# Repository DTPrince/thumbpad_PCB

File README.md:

# thumbpad_PCB
Repo for thumbstick PCB design

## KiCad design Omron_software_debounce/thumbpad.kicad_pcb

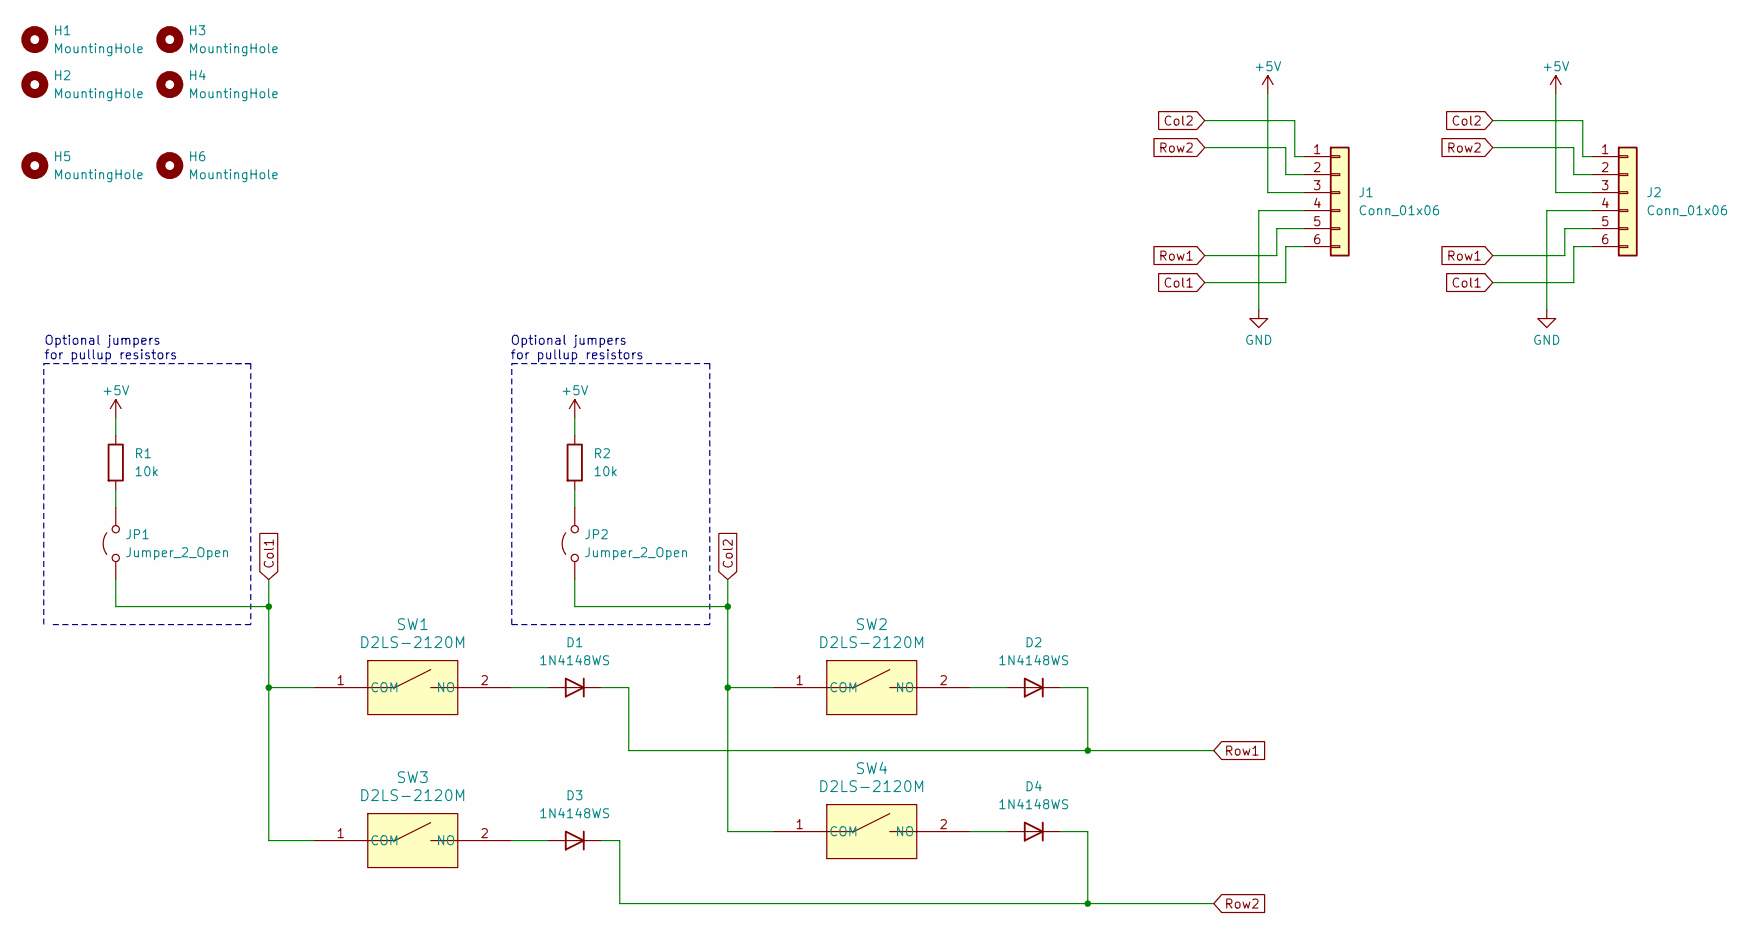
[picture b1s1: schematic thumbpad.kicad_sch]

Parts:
D1, D2, D3, D4: 1N4148WS; D_SOD-323
H1, H2, H3, H4: MountingHole; MountingHole_3.2mm_M3_ISO7380
H5, H6: MountingHole; MountingHole_1.6mm
J1: Conn_01x06; TEAmp-CON6-84953-SMT-RA-FCC-FPC
J2: Conn_01x06; pads_connector_0.1mm
JP1, JP2: Jumper_2_Open; SolderJumper-2_P1.3mm_Open_Pad1.0x1.5mm
R1, R2: 10k; R_0805_2012Metric_Pad1.20x1.40mm_HandSolder
SW1, SW2, SW3, SW4: D2LS-2120M; Omron_SW_D2LS_11_20M

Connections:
+5V: J1.3, J2.3, R1.1, R2.1
Col1: J1.6, J2.6, JP1.1 (A), SW1.1 (COM), SW3.1 (COM)
Col2: J1.1, J2.1, JP2.1 (A), SW2.1 (COM), SW4.1 (COM)
GND: J1.4, J2.4
unnamed: D1.2 (A), SW1.2 (NO)
unnamed: D2.2 (A), SW2.2 (NO)
unnamed: D3.2 (A), SW3.2 (NO)
unnamed: D4.2 (A), SW4.2 (NO)
unnamed: JP1.2 (B), R1.2
unnamed: JP2.2 (B), R2.2
Row1: D1.1 (K), D2.1 (K), J1.5, J2.5
Row2: D3.1 (K), D4.1 (K), J1.2, J2.2

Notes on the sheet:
Optional jumpers for pullup resistors

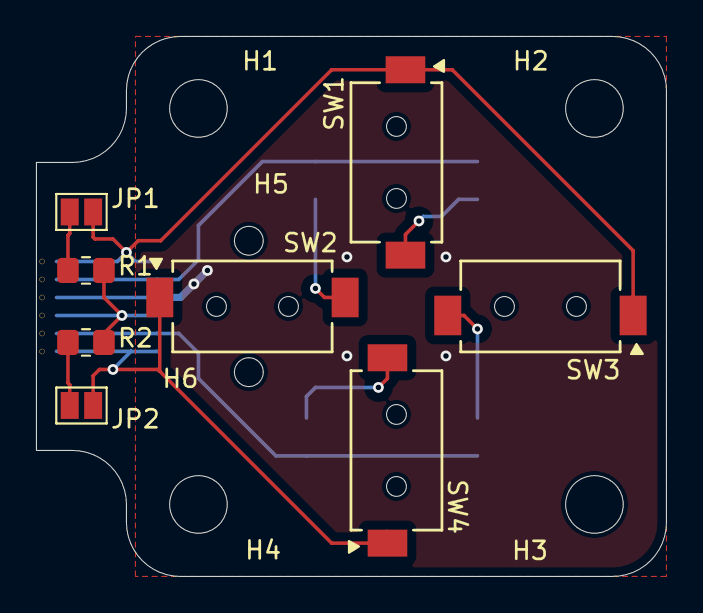
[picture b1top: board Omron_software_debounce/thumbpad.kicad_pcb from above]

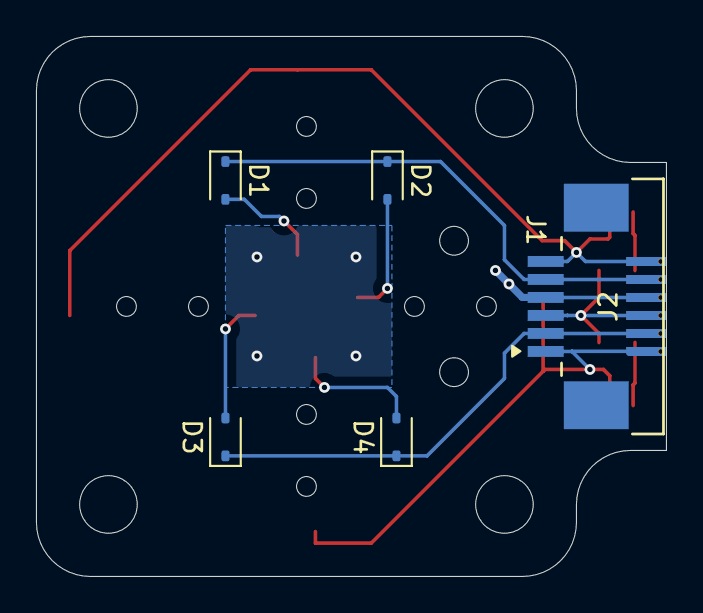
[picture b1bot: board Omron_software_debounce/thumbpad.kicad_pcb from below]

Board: 2 copper layers, 35.0 x 30.0 mm, 20 parts (6 on the bottom side), 12 nets.

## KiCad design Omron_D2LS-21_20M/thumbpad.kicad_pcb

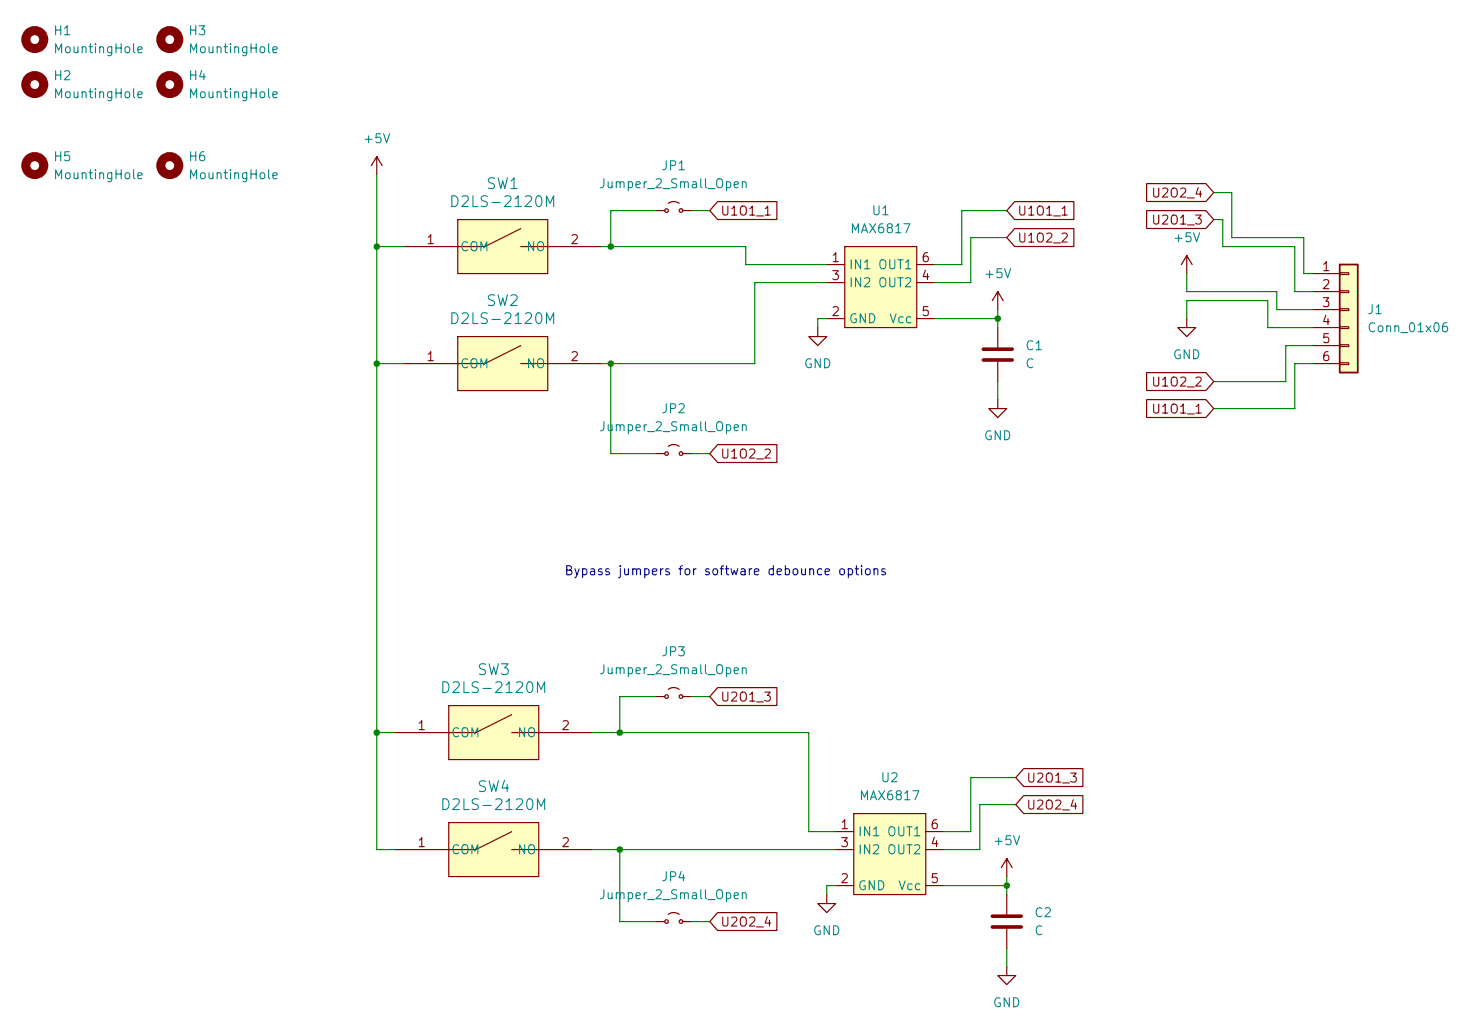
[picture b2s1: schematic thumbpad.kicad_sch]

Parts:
C1, C2: C; C_0805_2012Metric_Pad1.18x1.45mm_HandSolder
H1, H2, H3, H4: MountingHole; MountingHole_3.2mm_M3_ISO7380
H5, H6: MountingHole; MountingHole_1.6mm
J1: Conn_01x06; TEAmp-CON6-84953-SMT-RA-FCC-FPC
JP1, JP2, JP3, JP4: Jumper_2_Small_Open; SolderJumper-2_P1.3mm_Open_Pad1.0x1.5mm
SW1, SW2, SW3, SW4: D2LS-2120M; Omron_SW_D2LS_11_20M
U1, U2: MAX6817; SOT-23-6

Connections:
+5V: C1.1, C2.1, J1.3, SW1.1 (COM), SW2.1 (COM), SW3.1 (COM), SW4.1 (COM), U1.5 (Vcc), U2.5 (Vcc)
GND: C1.2, C2.2, J1.4, U1.2 (GND), U2.2 (GND)
unnamed: JP1.1 (A), SW1.2 (NO), U1.1 (IN1)
unnamed: JP2.1 (A), SW2.2 (NO), U1.3 (IN2)
unnamed: JP3.1 (A), SW3.2 (NO), U2.1 (IN1)
unnamed: JP4.1 (A), SW4.2 (NO), U2.3 (IN2)
U1O1_1: J1.6, JP1.2 (B), U1.6 (OUT1)
U1O2_2: J1.5, JP2.2 (B), U1.4 (OUT2)
U2O1_3: J1.2, JP3.2 (B), U2.6 (OUT1)
U2O2_4: J1.1, JP4.2 (B), U2.4 (OUT2)

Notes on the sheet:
Bypass jumpers for software debounce options

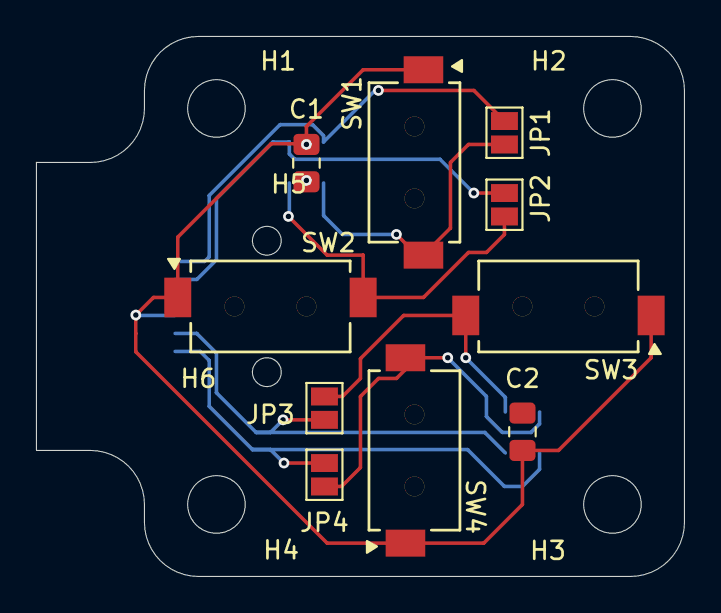
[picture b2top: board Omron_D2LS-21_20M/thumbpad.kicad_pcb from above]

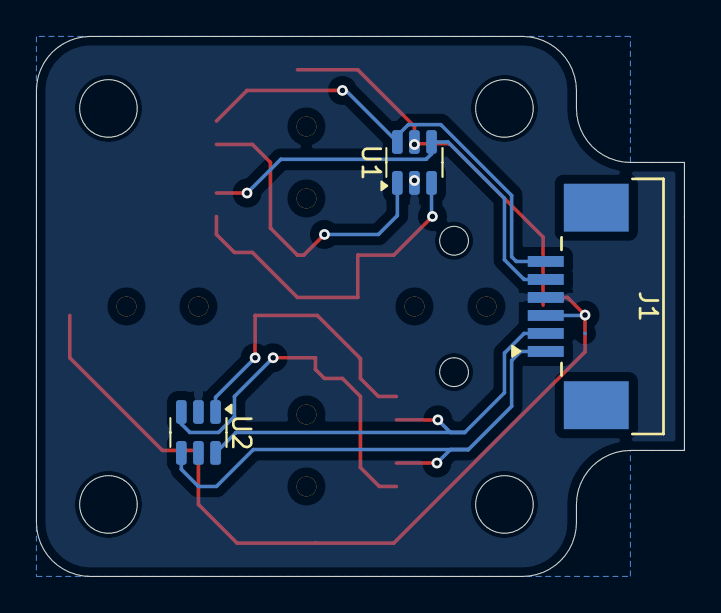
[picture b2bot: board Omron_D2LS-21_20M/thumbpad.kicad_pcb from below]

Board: 2 copper layers, 36.0 x 30.0 mm, 19 parts (3 on the bottom side), 10 nets.

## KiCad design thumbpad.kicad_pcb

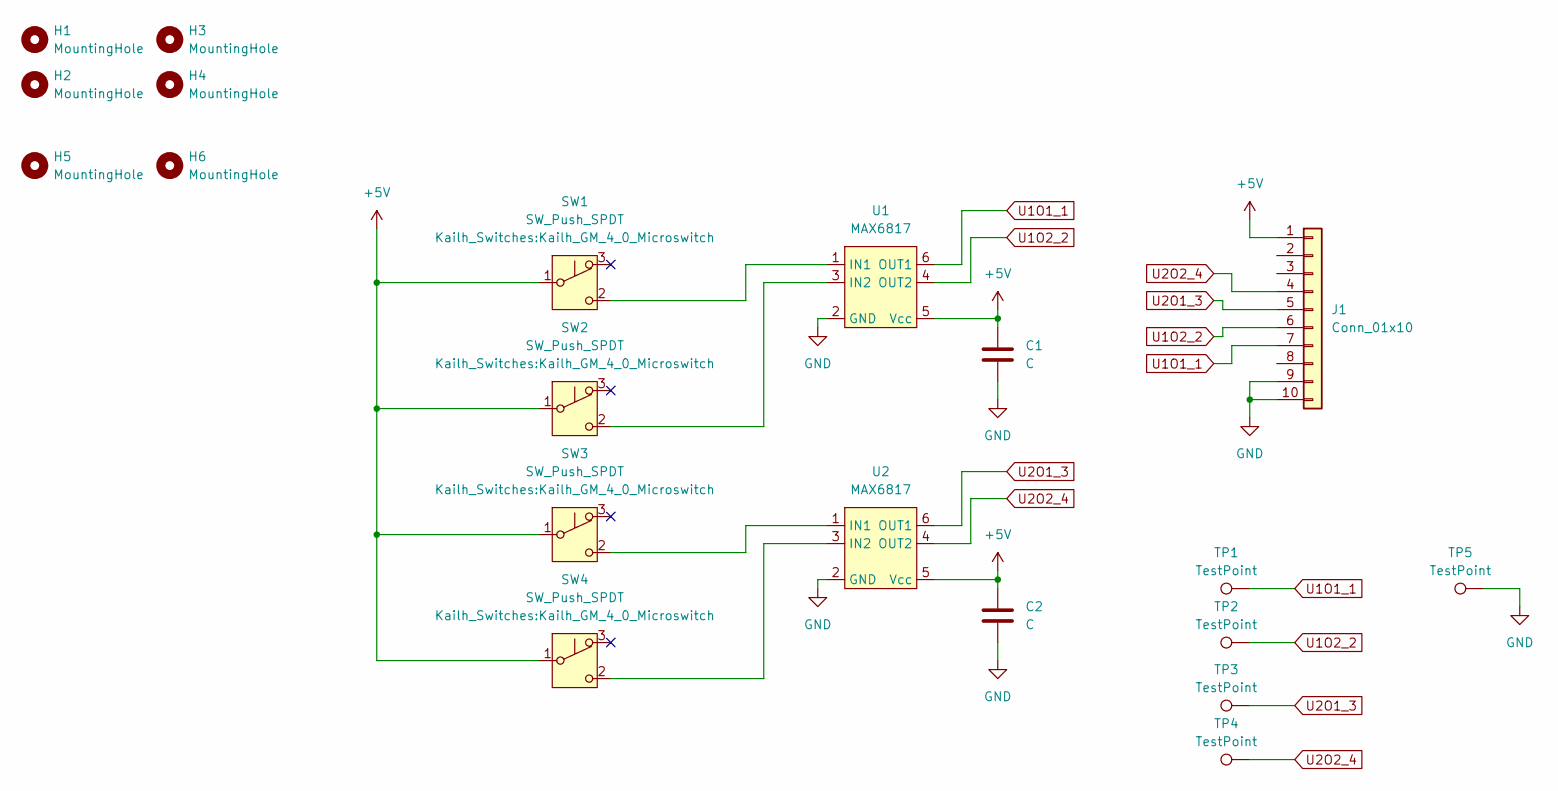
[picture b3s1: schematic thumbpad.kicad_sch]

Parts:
C1, C2: C; C_0805_2012Metric_Pad1.18x1.45mm_HandSolder
H1, H2, H3, H4: MountingHole; MountingHole_3.2mm_M3_ISO7380
H5, H6: MountingHole; MountingHole_1.6mm
J1: Conn_01x10; TE_1-84952-0_1x10-1MP_P1.0mm_Horizontal
SW1, SW2, SW3, SW4: SW_Push_SPDT; Kailh_GM_4_0_Microswitch
TP1, TP2, TP3, TP4: TestPoint; TestPoint_Pad_2.0x2.0mm
TP5: TestPoint; TestPoint_Loop_D2.60mm_Drill1.6mm_Beaded
U1, U2: MAX6817; SOT-23-6

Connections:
+5V: C1.1, C2.1, J1.1, SW1.1 (A), SW2.1 (A), SW3.1 (A), SW4.1 (A), U1.5 (Vcc), U2.5 (Vcc)
GND: C1.2, C2.2, J1.9, J1.10, TP5.1, U1.2 (GND), U2.2 (GND)
unnamed: SW1.2 (B), U1.1 (IN1)
unnamed: SW2.2 (B), U1.3 (IN2)
unnamed: SW3.2 (B), U2.1 (IN1)
unnamed: SW4.2 (B), U2.3 (IN2)
U1O1_1: J1.7, TP1.1, U1.6 (OUT1)
U1O2_2: J1.6, TP2.1, U1.4 (OUT2)
U2O1_3: J1.5, TP3.1, U2.6 (OUT1)
U2O2_4: J1.4, TP4.1, U2.4 (OUT2)

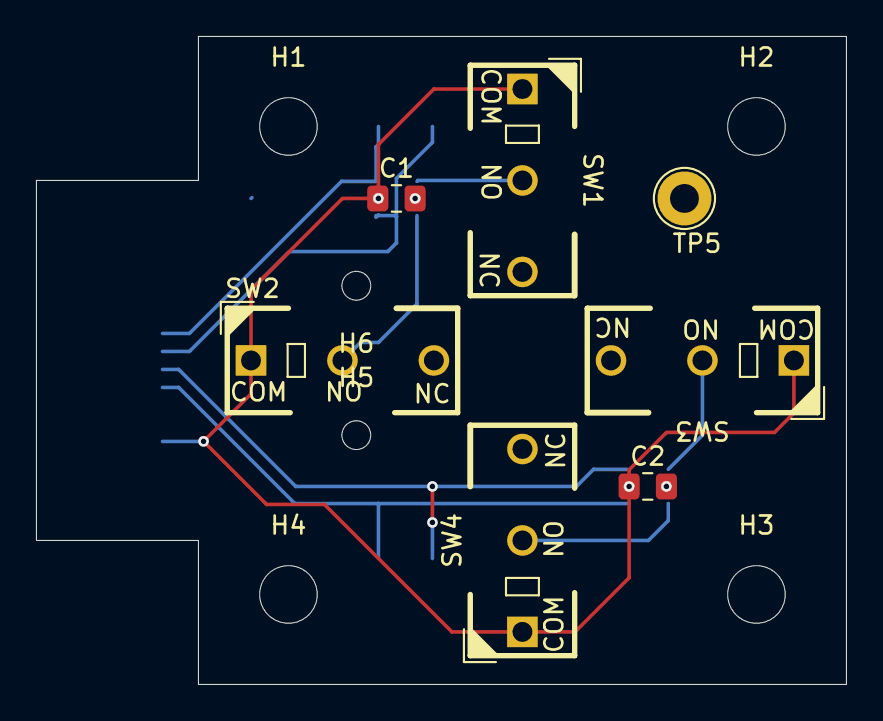
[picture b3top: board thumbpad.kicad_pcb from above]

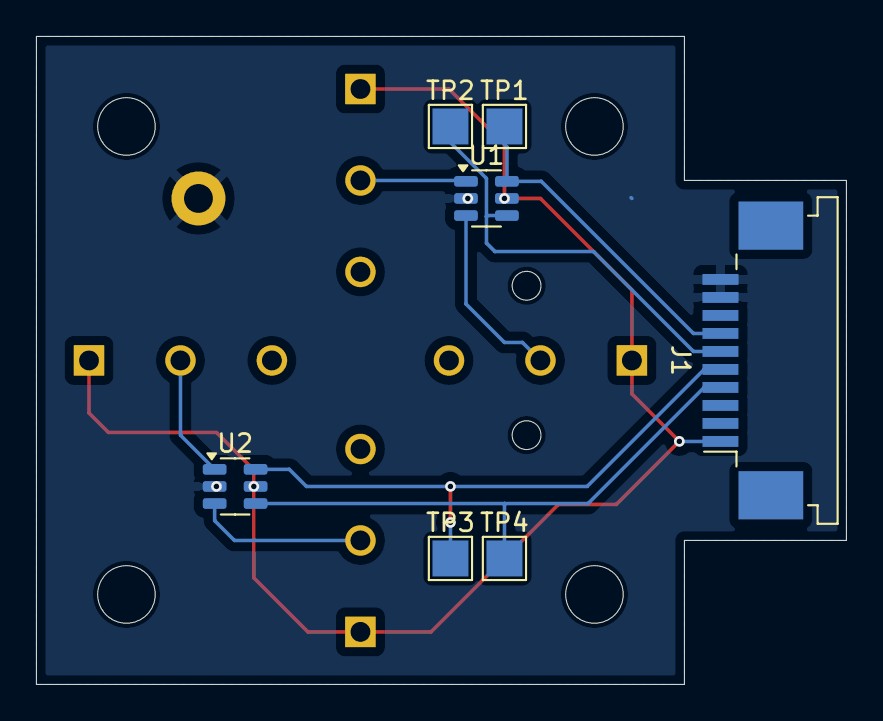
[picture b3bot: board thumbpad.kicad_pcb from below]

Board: 2 copper layers, 45.0 x 36.0 mm, 20 parts (7 on the bottom side), 10 nets.

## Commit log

2024-06-04 Initial design
    initial design upload
2024-06-11 File shuffle + small SW added
    moved larger switch project into own file Kialh file. New omron micro switches project made.
2024-06-11 6pos connector added, board shrink
2024-06-12 board shrunk/final shape v1
2024-06-12 Added jumpers to bypass debouncers
    Debouncing ICs are expensive, allows for software debounce option
2024-06-12 cosmetic update
2024-06-13 Updated to keyboard array connections
    Updated footprint to use 2x2 row/col layout for keyboard input. Optional 10k resistors + jumpers to make a 5v pull-up on the columns.
2024-06-28 Added pth pads for hand solder/pin headers
